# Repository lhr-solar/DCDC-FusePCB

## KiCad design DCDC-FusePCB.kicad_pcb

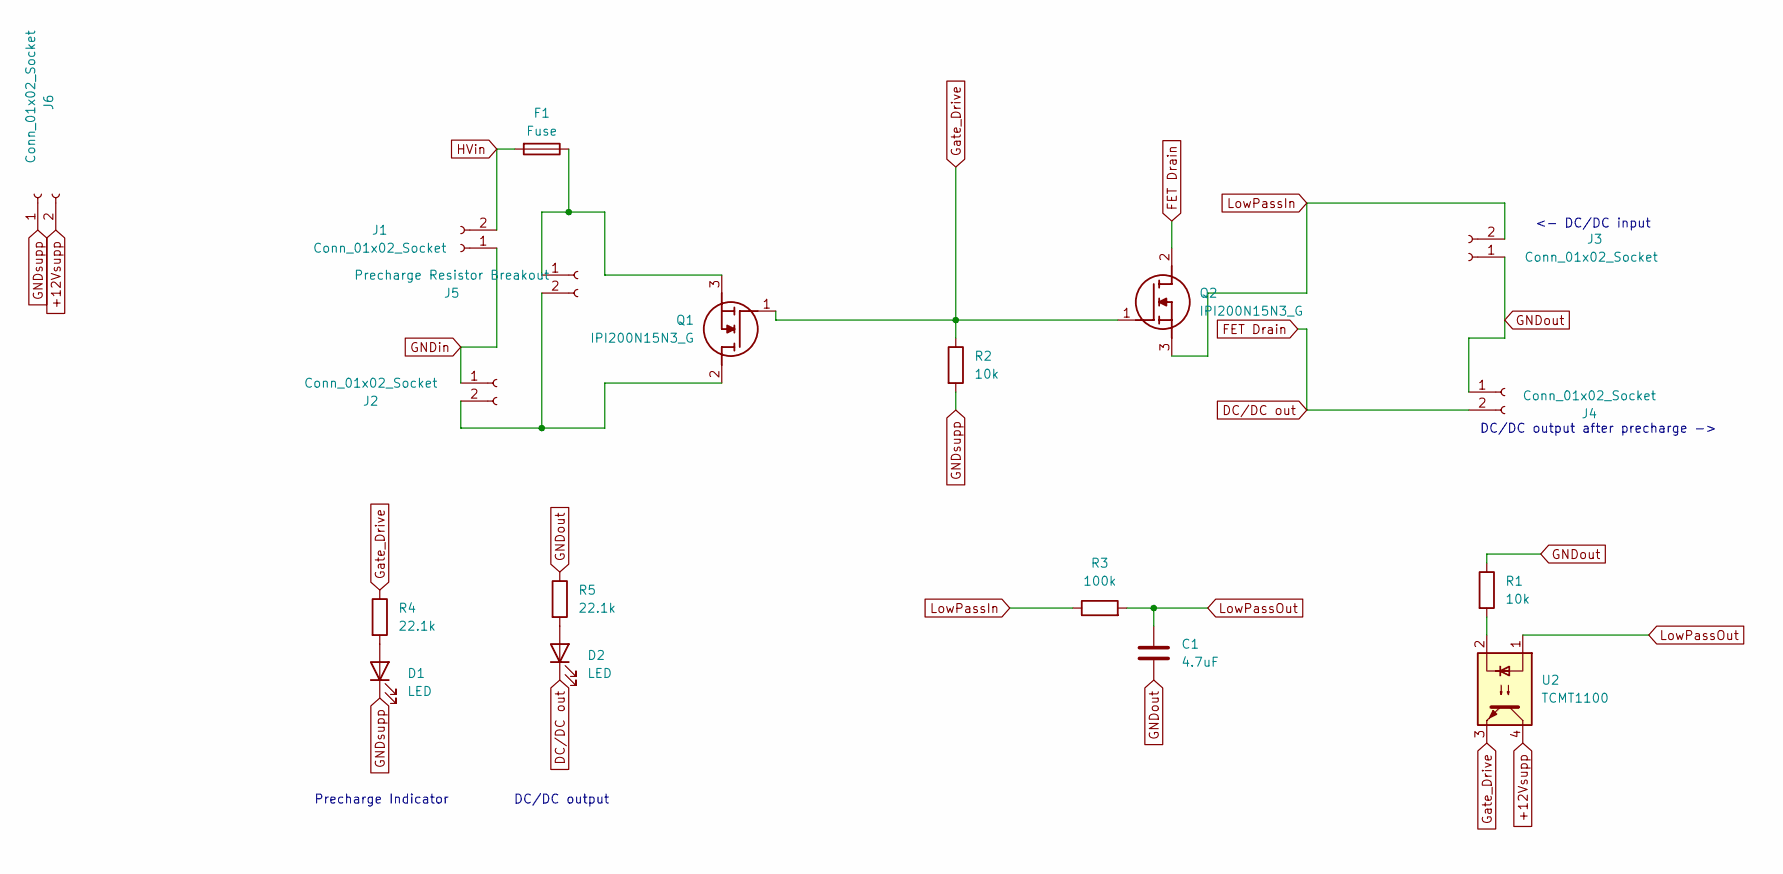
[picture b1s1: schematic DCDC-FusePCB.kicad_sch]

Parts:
C1: 4.7uF; C_0805_2012Metric
D1, D2: LED; LED_0805_2012Metric
F1: Fuse; FUSE_05200101Z_LTF
J1, J2, J3, J4, J6: Conn_01x02_Socket; Molex_Sabre_43160-0102_1x02_P7.49mm_Vertical
J5: Precharge Resistor Breakout; Molex_Sabre_43160-0102_1x02_P7.49mm_Vertical
Q1, Q2: IPI200N15N3_G; TO-220-3_16P51X10P67_ONS; Manufacturer_Part_Number IPI200N15N3 G
R1, R2: 10k; R_0805_2012Metric
R3: 100k; R_0805_2012Metric
R4, R5: 22.1k; R_0805_2012Metric
U2: TCMT1100; SOP-4_4.4x2.6mm_P1.27mm

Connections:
+12Vsupp: J6.2, U2.4
DC/DC out: D2.1 (K), J4.2, Q2.2 (D)
GNDin: J1.1, J2.1
GNDout: C1.2, J3.1, J4.1, R1.1, R5.1
GNDsupp: D1.1 (K), J6.1, R2.2
Gate_Drive: Q1.1 (G), Q2.1 (G), R2.1, R4.1, U2.3
HVin: F1.2, J1.2
LowPassIn: J3.2, Q2.3 (S), R3.1
LowPassOut: C1.1, R3.2, U2.1
unnamed: D1.2 (A), R4.2
unnamed: D2.2 (A), R5.2
unnamed: J2.2, J5.2, Q1.2 (D)
unnamed: F1.1, J5.1, Q1.3 (S)
unnamed: R1.2, U2.2

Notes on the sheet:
Precharge Indicator
DC/DC output
<- DC/DC input
DC/DC output after precharge ->

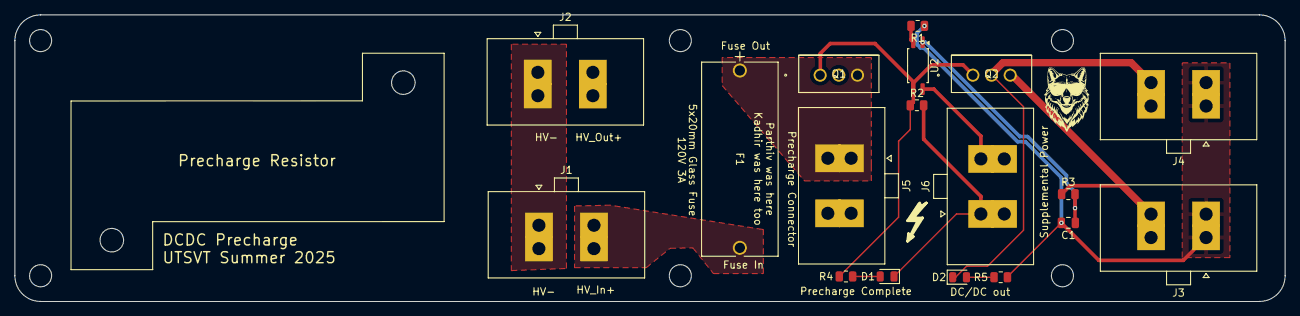
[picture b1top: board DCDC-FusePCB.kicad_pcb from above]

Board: 2 copper layers, 172.9 x 39.0 mm, 20 parts (0 on the bottom side), 14 nets.

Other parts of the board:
RH1, RH2: MountingHole; MountingHole_3.2mm_M3

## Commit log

2024-03-19 DC-DC fuse PCB
2024-03-19 DCDC board
2024-03-19 fixed edgecut layer
2024-03-19 add submodule UTSVT-KiCadLibraries
2024-03-19 Update UTSVT-KiCadLibraries
2024-03-19 update 3d file paths
2024-03-19 footprint and syumbol library path update
2024-03-19 Create test
2024-03-19 Rename test to test.yaml
2024-03-20 Updated Exports
2024-03-20 Rename FreeCAD Script.py to convert_step_to_png.py
2024-03-22 Updated PCB .png
2024-04-11 Updated PCB 3D Files
2025-03-23 replaced conns with screw terminals
2025-04-01 mountinghole pads design
2025-04-01 gerbs
2025-06-10 precharge board
2025-06-10 precharge board with resistor
2025-06-13 filled zones
